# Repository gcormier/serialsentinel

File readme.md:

### Early Access - still working on the esphome logic, but the hardware is working and documented.

# Serial Sentinel
Allows you full control of your computer's power button and reset button, remotely. Exposes a serial power that lets you run a watchdog and restart your computer in the event of a lockup. Or, send commands to hard-reset, power on or power off whenever you'd like.

## Specs
In a nutshell,

- PCIe x1 card
  - Low-profile / slim size
  - Should fit in servers, please verify
  - Runs off 3.3VAUX, which keeps powering the device, even when your PC shuts down
- WiFi with external antenna
- 2 serial ports exposed
  - One for esphome serial logging and programming
  - Another for heartbeat communications
  - WCH382L PCIe-Serial bridge (native Linux support, optional Linux driver, requires Windows driver)
- 3.3V voltage monitor
  - Good indicator if the computer is powered on or not
- PCIe wake output
  - Another option to wake up your computer
- Two relays with dual sets of pin headers
  - Intercept and passthrough your PC's power button and reset button
  - "push" either of those buttons remotely
- Two user status LED's
- Two LED's indicating power status of computer
- External 3.3V and 5V input in case you need creative options for "always-on" power supply
  - eg. You could tap the 5VSB from your ATX PSU if your motherboard does not provide 3V3AUX for some reason, or has a weak 3V3AUX rail.
- Optional beeper
- Many solderable jumpers to configure power supply settings in case your motherboard is weird

# Physical Installation
1. Always ensure your computer is fully powere off (eg ATX PSU is off) before installing the card. This card uses the 3.3VAUX rail, which is *always* powered on when the PSU is plugged in.
2. Insert the card into a free PCIe x1 slot.
3. Intercept your power button and/or reset button cables and connect them to the card. You can use any method, but easiest would be to use premade ["DuPont" cables](https://www.amazon.ca/s?k=dupont+connector+female+to+make) of various termination styles and lengths (eg. female-male, female-female).
4. Turn on your power supply.
5. With your computer still "off" (but with the power supply on), ensure you can see a green light on Serial Sentinel. This means you have 3.3VAUX power and can proceed.
    - You *MAY* need to run your computer through 1 valid power-on and power-off sequence to ensure the 3.3VAUX rail activated by your motherboard.
    - If you don't have a green light, you will likely need to source the power from elsewhere.
    - If you have an internal USB header that is "always on", you can use that to power the card using the 5V input.
    - You can also [tap](https://www.amazon.ca/t-tap-wire-connectors/s?k=t+tap+wire+connectors) a 3.3V wire from your [ATX PSU](https://en.wikipedia.org/wiki/ATX#Power_supply), and use it on the card's 3.3V input.
    - Do NOT use both the 5V and 3.3V inputs on the card. Use only 1.

## WiFi Antenna
An external antenna can be attached carefully to the ESP32-C3 using a [u.FL to SMA](https://www.amazon.ca/s?k=u.fl+to+sma+connector) cable. Any standard 2.4GHz SMA antenna will work. You can either use the included cutouts on the PCB to zip tie the antenna, or 3D print a bracket, or use an old/existing bracket and drill a 1/4" (6.35mm) hole to fit the SMA side of the cable connector.

# Software Installation
## Device ID and serial port
First, make sure you can see the device

```
$ lspci | grep CH382
03:00.0 Serial controller: Nanjing Qinheng Microelectronics Co., Ltd. CH352/CH382 PCI/PCIe Dual Port Serial Adapter (rev 10)
```

Find out which serial ports the device has created.
```
$ sudo dmesg | grep ttyS
[    0.496389] serial8250: ttyS1 at I/O 0x2f8 (irq = 3, base_baud = 115200) is a 16550A
[    0.498301] 0000:03:00.0: ttyS4 at I/O 0xd0c0 (irq = 17, base_baud = 115200) is a XR16850
[    0.500166] 0000:03:00.0: ttyS5 at I/O 0xd0c8 (irq = 17, base_baud = 115200) is a XR16850
```

In this case, ttyS4 and ttyS5 are the two serial ports. S4 is the native ESP32 serial port, which would be used for any logging or flashing over serial. S5 is the port you should use as communications for heartbeat and commands/etc based on the code you have running on the ESP32.

## First Flash
Sanity check that esptool can see and talk to the device.

```
$ esptool.py --port /dev/ttyS4 chip_id
esptool.py v4.8.1
Serial port /dev/ttyS4
Connecting....
Detecting chip type... ESP32-C3
Chip is ESP32-C3 (QFN32) (revision v0.4)
Features: WiFi, BLE
Crystal is 40MHz
MAC: b4:3a:45:4c:3f:f4
Uploading stub...
Running stub...
Stub running...
Warning: ESP32-C3 has no Chip ID. Reading MAC instead.
MAC: b4:3a:45:4c:3f:f4
Hard resetting via RTS pin...
```
If you see the above, you are ready to flash the firmware. If you don't see the device, check your serial port and ensure you have the right one.

Recommended baud rate is 115,200 for any flashing over serial.

# Common Questions
## Do I need a smarthome?
Nope. You can use the device without any smarthome integration. It can be used as a standalone device to control your computer's power and reset buttons, and you can program it to do various tasks based on the serial commands it receives.

## Do I need WiFi?
Nope. You can program the device to act on it's own based on the various inputs/conditions. You can do this with esphome, or with the Arduino framework or ESP-IDF. WiFi is only needed if you want to control the device remotely.

## Do I need drivers?
  - Linux will support the WCH382L serial bridge natively, so no drivers are needed. WCH does provide [Linux drivers](https://github.com/WCHSoftGroup/ch35_38x_linux), but they are not needed and seem to cause more trouble than it's worth.
  - Windows will require the WCH382L drivers to be installed. You can find them on the [WCH website](https://www.wch-ic.com/downloads/CH38XDRV_EXE.html). I do not use Windows for this project, so I can't provide assistance.

## Do I need any software?
In theory you don't even need to use the serial ports (other then getting your code to the device). You could just flash esphome, and control the device yourself remotely.
Or you could hardcode some dumb logic to control the power and reset buttons based on the inputs you have available. 

More advanced usage would have you regularly sending
a heartbeat to the device, and the device would then be able to reset your computer if it stops receiving heartbeats.

# Troubleshooting

## Constantly resetting
The circuit has logic that will reset the device via DTR/RTS so that the initial firmware can be loaded with `esptool`.
If your operating system is sending signals, that can cause the device to reset, or remain in a reset state
which would be an unresponsive state. You can try to prevent this with software. Or, after the first flash, you can remove the DTR/RTS jumpers on the PCB to prevent this from happening and keep updating the device over WiFi.

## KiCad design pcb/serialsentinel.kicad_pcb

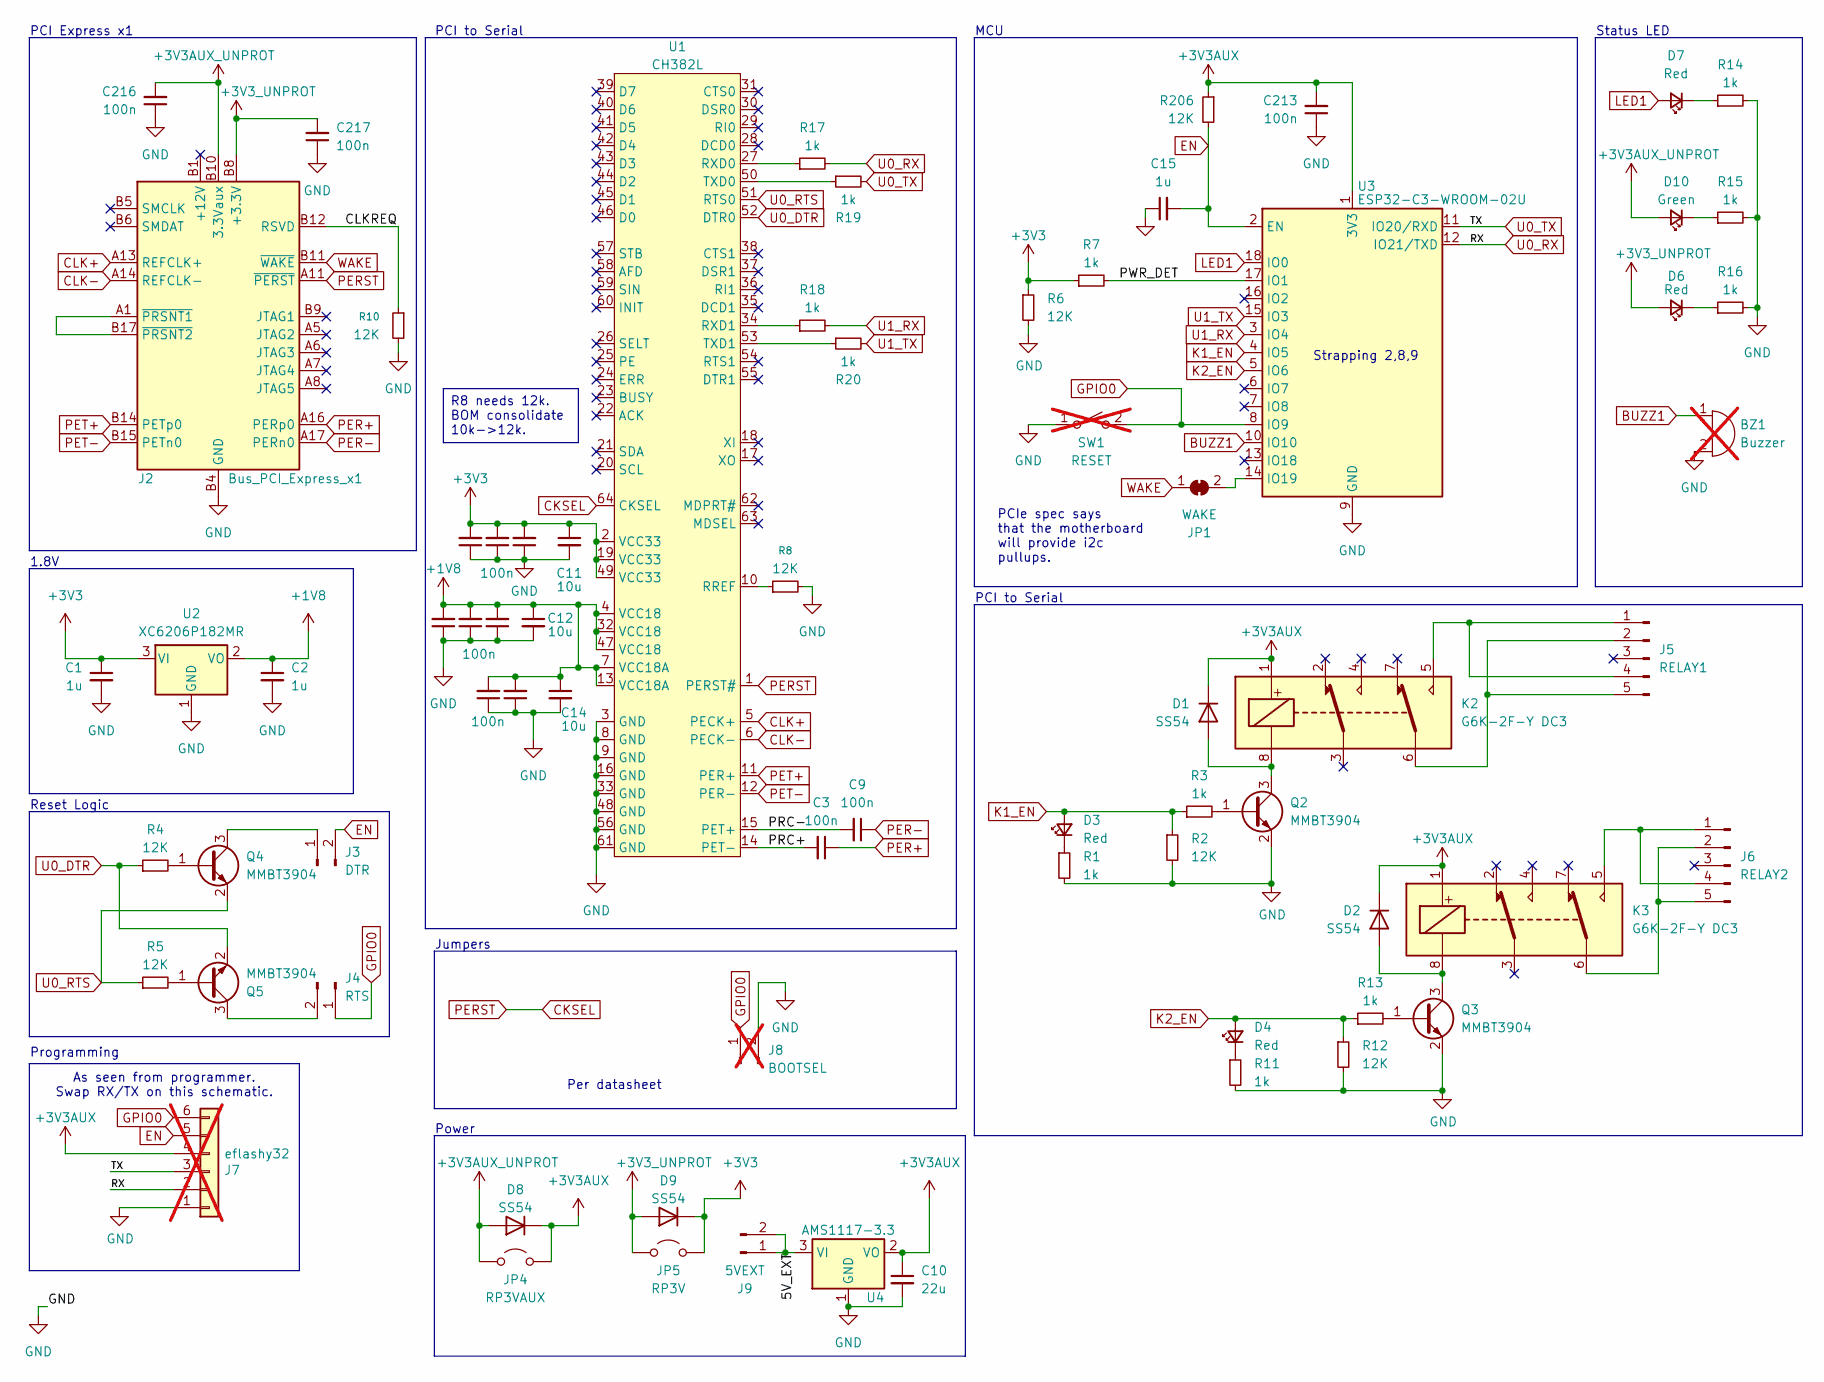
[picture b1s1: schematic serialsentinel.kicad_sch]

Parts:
BZ1: Buzzer; MagneticBuzzer_PUI_AT-0927-TT-6-R; LCSC C96256; not fitted
C1, C2, C15: 1u; C_0402_1005Metric; LCSC C52923
C3, C4, C5, C6, C7, C8, C9, C13, C213, C214, C215, C216, C217: 100n; C_0402_1005Metric; LCSC C307331
C10: 22u; C_0603_1608Metric; LCSC C59461
C11, C12, C14: 10u; C_0402_1005Metric; LCSC C15525
D1, D2, D8, D9: SS54; D_SMA; LCSC C22452
D3, D4, D6, D7: Red; LED_0805_2012Metric; LCSC C84256
D10: Green; LED_0805_2012Metric; LCSC C2297
J2: Bus_PCI_Express_x1; BUS_PCIexpress_x1
J3: DTR; PinHeader_1x02_P2.54mm_Vertical; LCSC C27985187
J4: RTS; PinHeader_1x02_P2.54mm_Vertical; LCSC C27985187
J5: RELAY1; PinHeader_1x05_P2.54mm_Horizontal; LCSC C492413
J6: RELAY2; PinHeader_1x05_P2.54mm_Horizontal; LCSC C492413
J7: eflashy32; PinHeader_1x06_P2.54mm_Vertical; not fitted
J8: BOOTSEL; PinHeader_1x02_P2.54mm_Vertical; not fitted
J9: 5VEXT; PinHeader_1x02_P2.54mm_Vertical; LCSC C27985187
JP1: WAKE; SolderJumper-2_P1.3mm_Bridged_RoundedPad1.0x1.5mm
JP4: RP3VAUX; SolderJumper-2_P1.3mm_Open_RoundedPad1.0x1.5mm
JP5: RP3V; SolderJumper-2_P1.3mm_Open_RoundedPad1.0x1.5mm
K2, K3: G6K-2F-Y DC3; Relay_DPDT_Omron_G6K-2F-Y; LCSC C2153097
Q2, Q3, Q4, Q5: MMBT3904; SOT-23; LCSC C20526
R1, R3, R7, R11, R13, R14, R15, R16, R17, R18, R19, R20: 1k; R_0402_1005Metric; LCSC C11702
R2, R4, R5, R6, R8, R10, R12, R206: 12K; R_0402_1005Metric; LCSC C25752
SW1: RESET; SW_Push_1P1T_XKB_TS-1187A; LCSC C318884; not fitted
U1: CH382L; LQFP-64_7x7mm_P0.4mm; LCSC C2685237
U2: XC6206P182MR; SOT-23-3; LCSC C347373
U3: ESP32-C3-WROOM-02U; LCSC C2926676
U4: AMS1117-3.3; SOT-223-3_TabPin2; LCSC C6186

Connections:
+1V8: C2.1, C4.2, C6.2, C8.2, C12.1, C13.2, C14.1, C214.2, U1.4 (VCC18), U1.7 (VCC18A), U1.13 (VCC18A), U1.32 (VCC18), U1.47 (VCC18), U2.2 (VO)
+3V3: C1.1, C5.2, C7.2, C11.1, C215.2, D9.1 (K), JP5.2 (B), R6.1, R7.1, U1.2 (VCC33), U1.19 (VCC33), U1.49 (VCC33), U2.3 (VI)
+3V3AUX: C10.1, C213.2, D1.1 (K), D2.1 (K), D8.1 (K), J7.4, JP4.2 (B), K2.1, K3.1, R206.1, U3.1 (3V3), U4.2 (VO)
+3V3AUX_UNPROT: C216.2, D8.2 (A), D10.2 (A), J2.B10 (3.3Vaux), JP4.1 (A)
+3V3_UNPROT: C217.2, D6.2 (A), D9.2 (A), J2.A9 (+3.3V), J2.A10 (+3.3V), J2.B8 (+3.3V), JP5.1 (A)
/5V_EXT: J9.1, J9.2, U4.3 (VI)
/CLKREQ: J2.B12 (RSVD), R10.1
/PRC+: C3.2, U1.14 (PET-)
/PRC-: C9.2, U1.15 (PET+)
/PWR_DET: R7.2, U3.17 (IO1)
BUZZ1: BZ1.1 (+), U3.10 (IO10)
CKSEL: J2.A11 (~PERST), U1.1 (PERST#), U1.64 (CKSEL)
CLK+: J2.A13 (REFCLK+), U1.5 (PECK+)
CLK-: J2.A14 (REFCLK-), U1.6 (PECK-)
EN: C15.2, J3.2, J7.5, R206.2, U3.2 (EN)
GND: BZ1.2 (-), C1.2, C2.2, C4.1, C5.1, C6.1, C7.1, C8.1, C10.2, C11.2, C12.2, C13.1, C14.2, C15.1, C213.1, C214.1, C215.1, C216.1, C217.1, J2.A4 (GND), J2.A12 (GND), J2.A15 (GND), J2.A18 (GND), J2.B4 (GND), J2.B7 (GND), J2.B13 (GND), J2.B16 (GND), J2.B18 (GND), J7.1, J8.2, Q2.2 (E), Q3.2 (E), R1.2, R2.2, R6.2, R8.2, R10.2, R11.2, R12.2, R14.2, R15.2, R16.2, SW1.1 (A), U1.3 (GND), U1.8 (GND), U1.9 (GND), U1.16 (GND), U1.33 (GND), U1.48 (GND), U1.56 (GND), U1.61 (GND), U2.1 (GND), U3.9 (GND), U3.19 (GND), U4.1 (GND)
GPIO0: J4.1, J7.6, J8.1, SW1.2 (B), U3.8 (IO9)
K1_EN: D3.2 (A), R2.1, R3.1, U3.4 (IO5)
K2_EN: D4.2 (A), R12.1, R13.1, U3.5 (IO6)
LED1: D7.2 (A), U3.18 (IO0)
unnamed: D1.2 (A), K2.8, Q2.3 (C)
unnamed: D2.2 (A), K3.8, Q3.3 (C)
unnamed: D3.1 (K), R1.1
unnamed: D4.1 (K), R11.1
unnamed: D6.1 (K), R16.1
unnamed: D7.1 (K), R14.1
unnamed: D10.1 (K), R15.1
unnamed: J2.A1 (~PRSNT1), J2.B17 (~PRSNT2)
unnamed: J3.1, Q4.3 (C)
unnamed: J4.2, Q5.3 (C)
unnamed: J5.1, J5.4, K2.5
unnamed: J5.2, J5.5, K2.6
unnamed: J6.1, J6.4, K3.5
unnamed: J6.2, J6.5, K3.6
unnamed: JP1.2 (B), U3.14 (IO19)
unnamed: Q2.1 (B), R3.2
unnamed: Q3.1 (B), R13.2
unnamed: Q4.1 (B), R4.2
unnamed: Q5.1 (B), R5.2
unnamed: R8.1, U1.10 (RREF)
unnamed: R17.1, U1.27 (RXD0)
unnamed: R18.1, U1.34 (RXD1)
unnamed: R19.1, U1.50 (TXD0)
unnamed: R20.1, U1.53 (TXD1)
PER+: C3.1, J2.A16 (PERp0)
PER-: C9.1, J2.A17 (PERn0)
PET+: J2.B14 (PETp0), U1.11 (PER+)
PET-: J2.B15 (PETn0), U1.12 (PER-)
U0_DTR: Q5.2 (E), R4.1, U1.52 (DTR0)
U0_RTS: Q4.2 (E), R5.1, U1.51 (RTS0)
U0_RX: J7.2, R17.2, U3.12 (IO21/TXD)
U0_TX: J7.3, R19.2, U3.11 (IO20/RXD)
U1_RX: R18.2, U3.3 (IO4)
U1_TX: R20.2, U3.15 (IO3)
WAKE: J2.B11 (~WAKE), JP1.1 (A)

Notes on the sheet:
As seen from programmer. Swap RX/TX on this schematic.
PCI to Serial
Status LED
PCIe spec says that the motherboard will provide i2c pullups.
Power
Programming
Strapping 2,8,9
PCI Express x1
Reset Logic
Jumpers
1.8V
Per datasheet
MCU
R8 needs 12k. BOM consolidate 10k->12k.

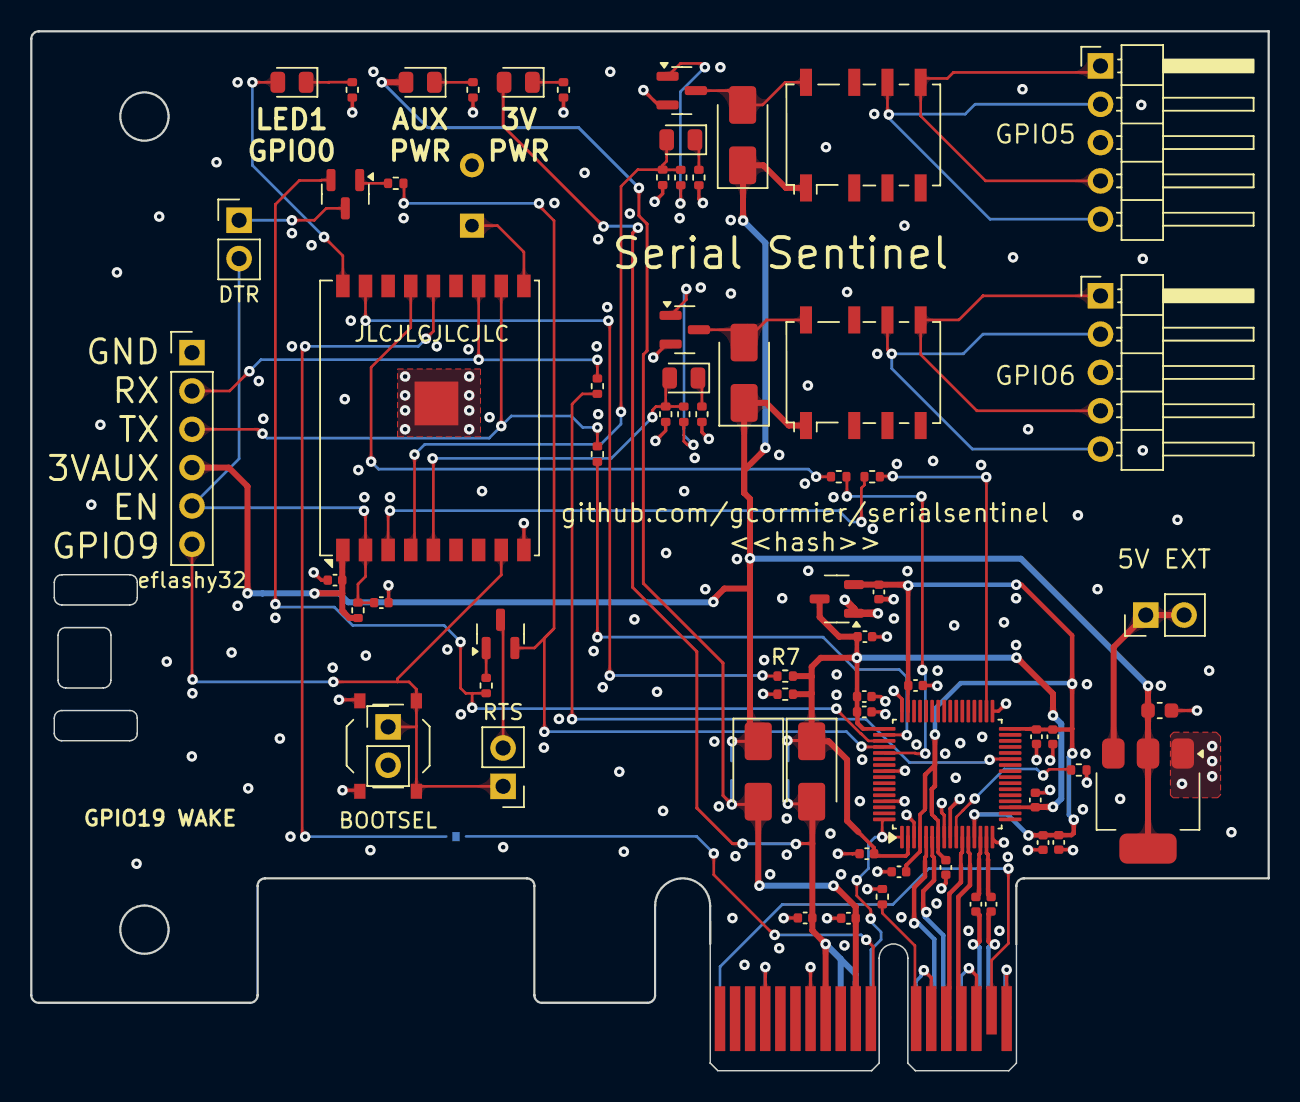
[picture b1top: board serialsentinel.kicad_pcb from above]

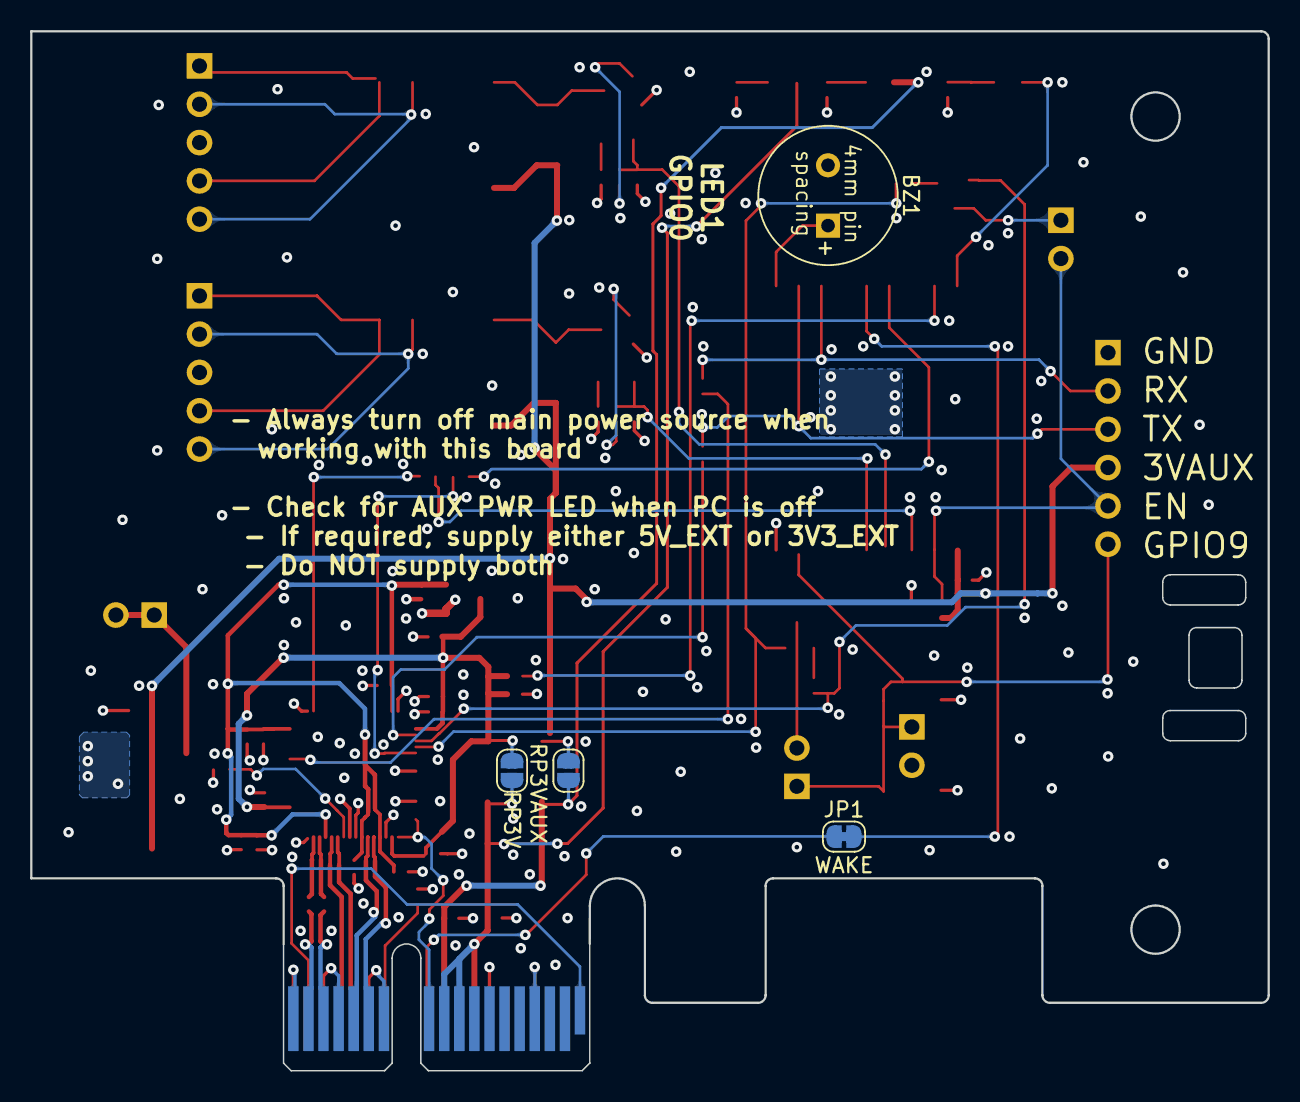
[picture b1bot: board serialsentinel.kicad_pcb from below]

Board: 4 copper layers, 82.0 x 68.9 mm, 72 parts (4 on the bottom side), 55 nets.

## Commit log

2025-05-10 initial
2025-05-10 tweak
2025-05-10 panel
2025-05-15 tweaks
2025-05-16 logo
2025-05-17 touchup
2025-05-22 final tweaks
2025-05-25 fix footprint
2025-06-15 fixes
2025-06-17 update kibot
2025-06-29 code
2025-07-03 towards v3!
2025-07-12 add PN for ams
2025-07-12 fix diode val
2025-07-29 fix things
2025-08-12 changes based on review pt 1
2025-08-12 final changes
2025-08-15 dunno
